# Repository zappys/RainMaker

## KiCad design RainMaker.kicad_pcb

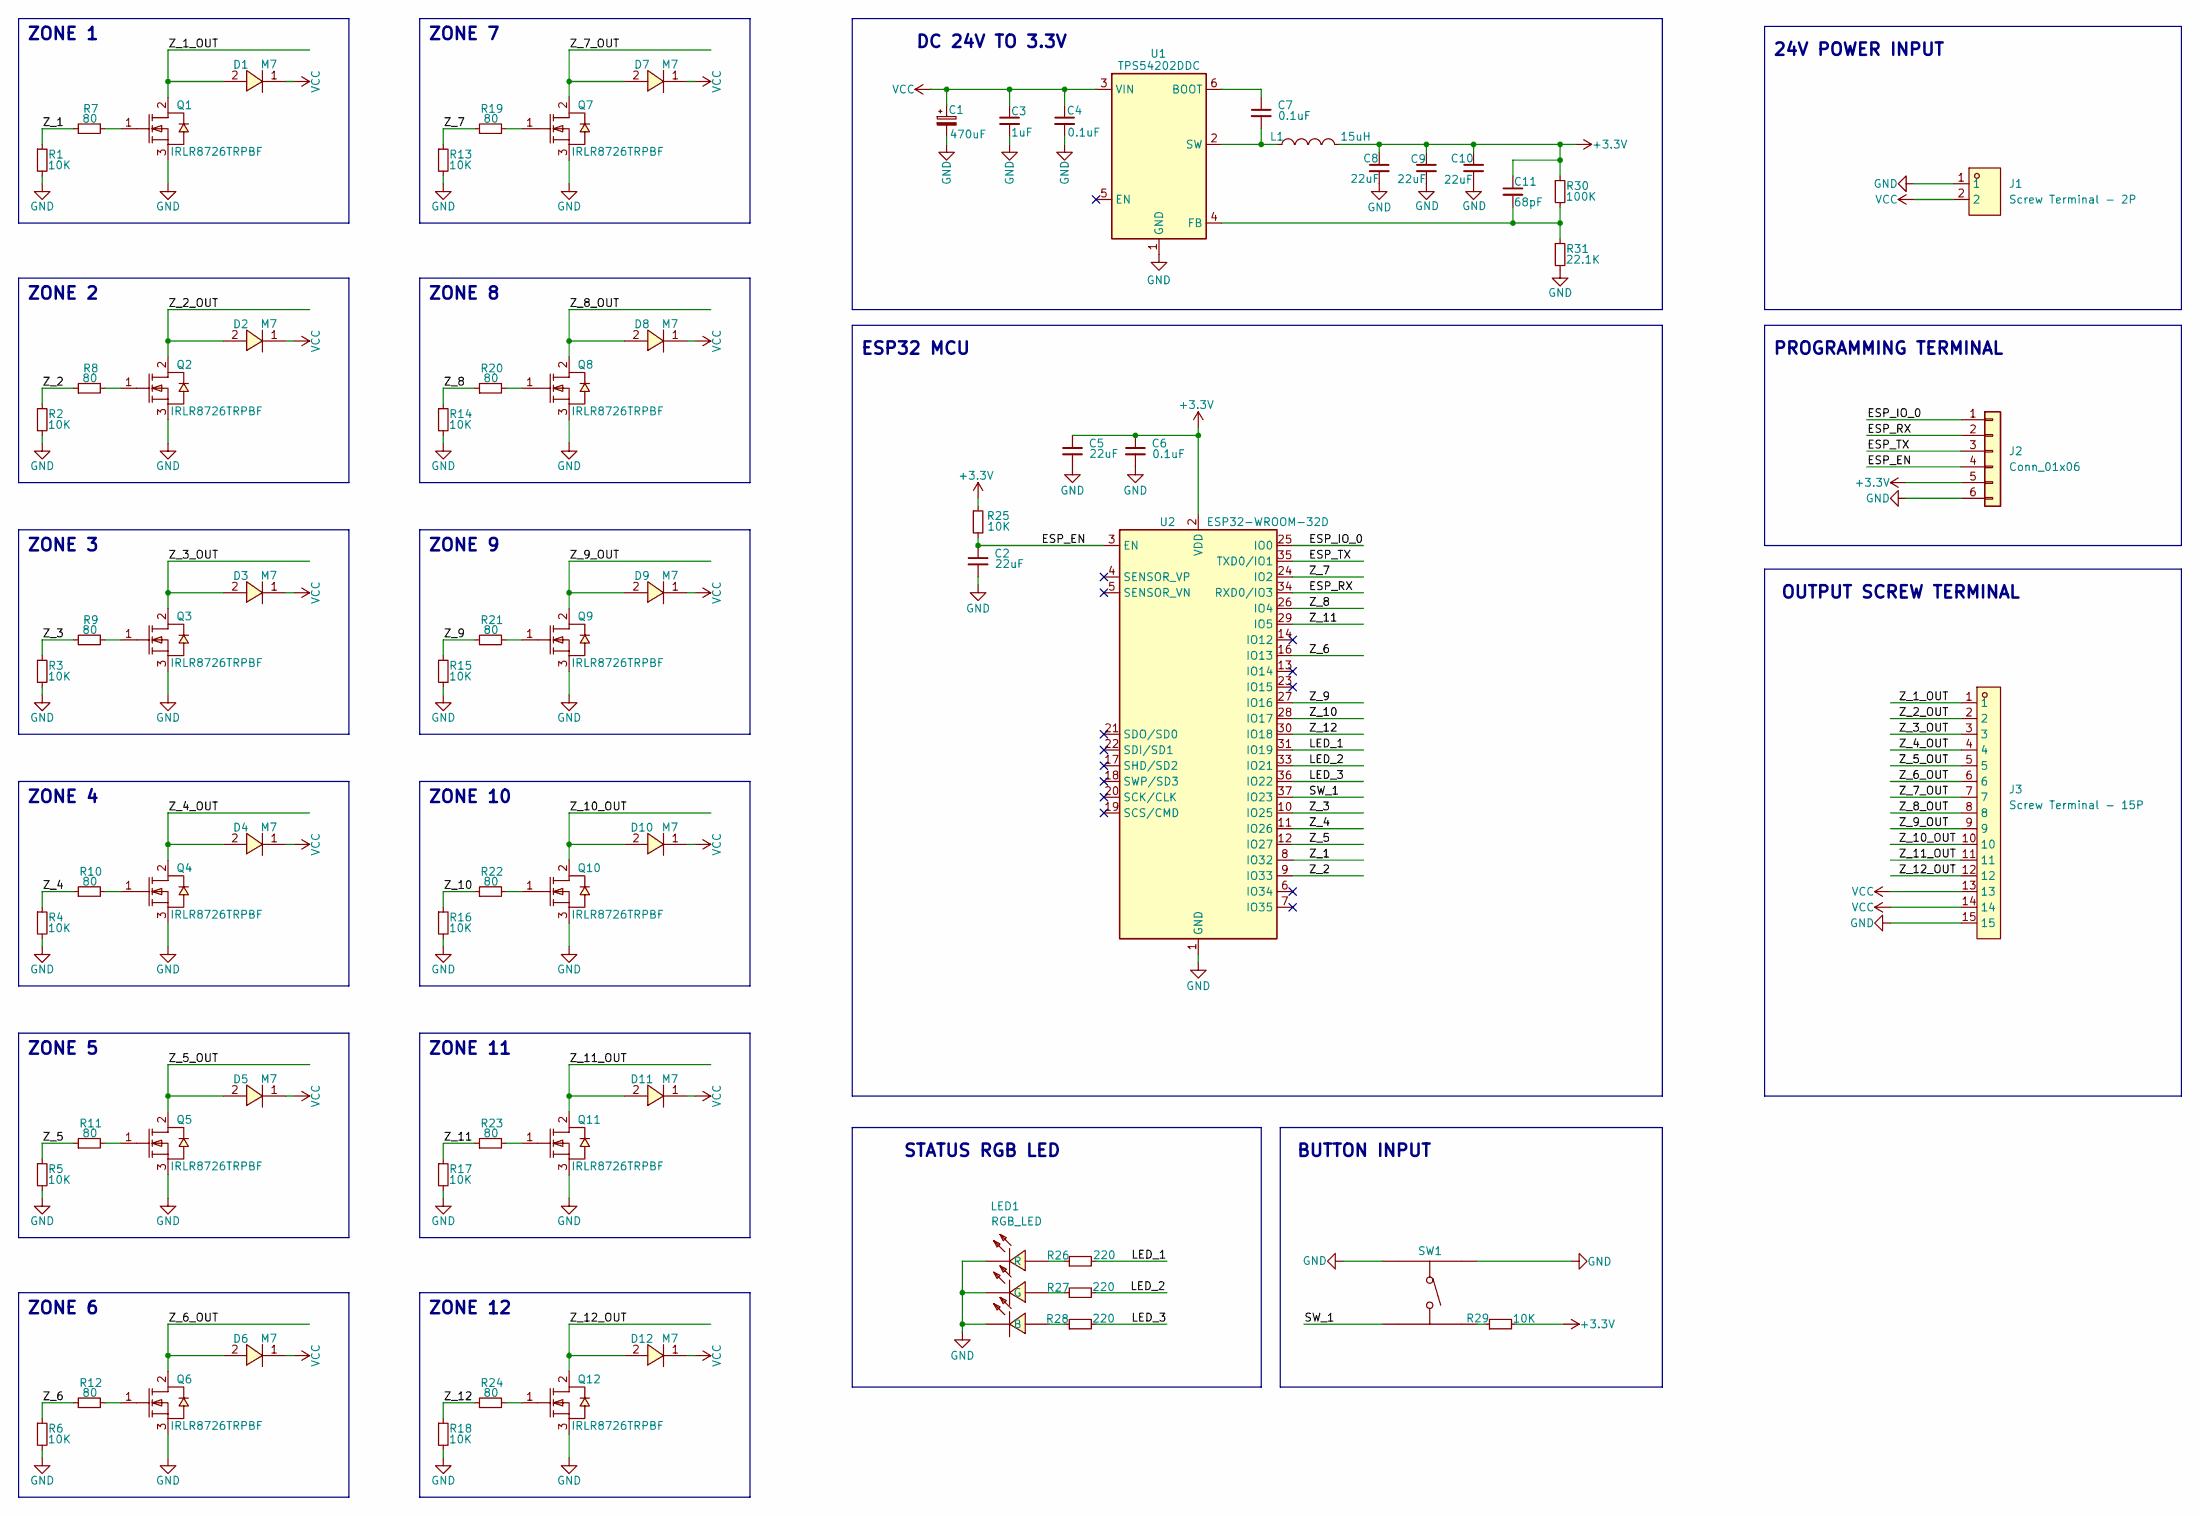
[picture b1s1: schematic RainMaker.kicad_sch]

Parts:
C1: 470uF; CP_Radial_D10.0mm_P5.00mm
C2, C5: 22uF; C_0805_2012Metric_Pad1.18x1.45mm_HandSolder
C3: 1uF; C_0805_2012Metric_Pad1.18x1.45mm_HandSolder
C4, C6, C7: 0.1uF; C_0805_2012Metric_Pad1.18x1.45mm_HandSolder
C8, C9, C10: 22uF; C_0805_2012Metric_Pad1.18x1.45mm_HandSolder; LCSC C45783
C11: 68pF; C_0805_2012Metric_Pad1.18x1.45mm_HandSolder
D1, D2, D3, D4, D5, D6, D7, D8, D9, D10, D11, D12: M7; SMA_L4.4-W2.6-LS5.0-RD; LCSC Part C426571
J1: Screw Terminal - 2P; CONN-TH_P5.08_KF128-5.08-2P; LCSC Part C474952
J2: Conn_01x06; PinHeader_1x06_P2.54mm_Vertical
J3: Screw Terminal - 15P; CONN-TH_15P-P5.00_DB128V; LCSC Part C424689
L1: 15uH; IND-SMD_L7.2-W6.6_GPSR07X0; LCSC Part C5189959
LED1: RGB_LED; LED-ARRAY-SMD_6P-L1.6-W1.6-TL; LCSC Part C131204
Q1, Q2, Q3, Q4, Q5, Q6, Q7, Q8, Q9, Q10, Q11, Q12: IRLR8726TRPBF; TO-252-2; LCSC Part C81137
R1, R2, R3, R4, R5, R6, R13, R14, R15, R16, R17, R18, R25, R29: 10K; R_0603_1608Metric
R7, R8, R9, R10, R11, R12, R19, R20, R21, R22, R23, R24: 80; R_0603_1608Metric
R26, R27, R28: 220; R_0603_1608Metric
R30: 100K; R_0603_1608Metric
R31: 22.1K; R_0603_1608Metric
SW1: UK-B0206-G5-250-JZ; KEY-SMD_4P-L4.5-W4.5-P3.00-LS7.5; LCSC Part C780491
U1: TPS54202DDC; SOT-23-6
U2: ESP32-WROOM-32D; ESP32-WROOM-32

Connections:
+3.3V: C5.1, C6.1, C8.1, C9.1, C10.1, C11.1, J2.5, L1.2, R25.1, R29.2, R30.1, U2.2 (VDD)
/ESP_EN: C2.1, J2.4, R25.2, U2.3 (EN)
/ESP_IO_0: J2.1, U2.25 (IO0)
/ESP_RX: J2.2, U2.34 (RXD0/IO3)
/ESP_TX: J2.3, U2.35 (TXD0/IO1)
/LED_1: R26.2, U2.31 (IO19)
/LED_2: R27.2, U2.33 (IO21)
/LED_3: R28.2, U2.36 (IO22)
/SW_1: SW1.3, U2.37 (IO23)
/Z_1: R1.1, R7.1, U2.8 (IO32)
/Z_1_OUT: D1.2, J3.1, Q1.2
/Z_2: R2.1, R8.1, U2.9 (IO33)
/Z_2_OUT: D2.2, J3.2, Q2.2
/Z_3: R3.1, R9.1, U2.10 (IO25)
/Z_3_OUT: D3.2, J3.3, Q3.2
/Z_4: R4.1, R10.1, U2.11 (IO26)
/Z_4_OUT: D4.2, J3.4, Q4.2
/Z_5: R5.1, R11.1, U2.12 (IO27)
/Z_5_OUT: D5.2, J3.5, Q5.2
/Z_6: R6.1, R12.1, U2.16 (IO13)
/Z_6_OUT: D6.2, J3.6, Q6.2
/Z_7: R13.1, R19.1, U2.24 (IO2)
/Z_7_OUT: D7.2, J3.7, Q7.2
/Z_8: R14.1, R20.1, U2.26 (IO4)
/Z_8_OUT: D8.2, J3.8, Q8.2
/Z_9: R15.1, R21.1, U2.27 (IO16)
/Z_9_OUT: D9.2, J3.9, Q9.2
/Z_10: R16.1, R22.1, U2.28 (IO17)
/Z_10_OUT: D10.2, J3.10, Q10.2
/Z_11: R17.1, R23.1, U2.29 (IO5)
/Z_11_OUT: D11.2, J3.11, Q11.2
/Z_12: R18.1, R24.1, U2.30 (IO18)
/Z_12_OUT: D12.2, J3.12, Q12.2
GND: C1.2, C2.2, C3.2, C4.2, C5.2, C6.2, C8.2, C9.2, C10.2, J1.1, J2.6, J3.15, LED1.1, LED1.2, LED1.3, Q1.3, Q2.3, Q3.3, Q4.3, Q5.3, Q6.3, Q7.3, Q8.3, Q9.3, Q10.3, Q11.3, Q12.3, R1.2, R2.2, R3.2, R4.2, R5.2, R6.2, R13.2, R14.2, R15.2, R16.2, R17.2, R18.2, R31.2, SW1.1, SW1.2, U1.1 (GND), U2.1 (GND), U2.15 (GND), U2.38 (GND), U2.39 (GND)
unnamed: LED1.6 (B), R28.1
unnamed: LED1.5 (G), R27.1
unnamed: LED1.4 (R), R26.1
unnamed: Q1.1, R7.2
unnamed: Q2.1, R8.2
unnamed: Q3.1, R9.2
unnamed: Q4.1, R10.2
unnamed: Q5.1, R11.2
unnamed: Q6.1, R12.2
unnamed: Q7.1, R19.2
unnamed: Q8.1, R20.2
unnamed: Q9.1, R21.2
unnamed: Q10.1, R22.2
unnamed: Q11.1, R23.2
unnamed: Q12.1, R24.2
unnamed: R29.1, SW1.4
unnamed: C7.1, U1.6 (BOOT)
unnamed: C11.2, R30.2, R31.1, U1.4 (FB)
unnamed: C7.2, L1.1, U1.2 (SW)
VCC: C1.1, C3.1, C4.1, D1.1, D2.1, D3.1, D4.1, D5.1, D6.1, D7.1, D8.1, D9.1, D10.1, D11.1, D12.1, J1.2, J3.13, J3.14, U1.3 (VIN)

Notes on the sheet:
ZONE 9
ZONE 3
ZONE 10
24V POWER INPUT
ZONE 7
ZONE 1
ZONE 4
ESP32 MCU
DC 24V TO 3.3V
STATUS RGB LED
ZONE 12
OUTPUT SCREW TERMINAL
ZONE 5
ZONE 6
ZONE 8
BUTTON INPUT
ZONE 11
ZONE 2
PROGRAMMING TERMINAL

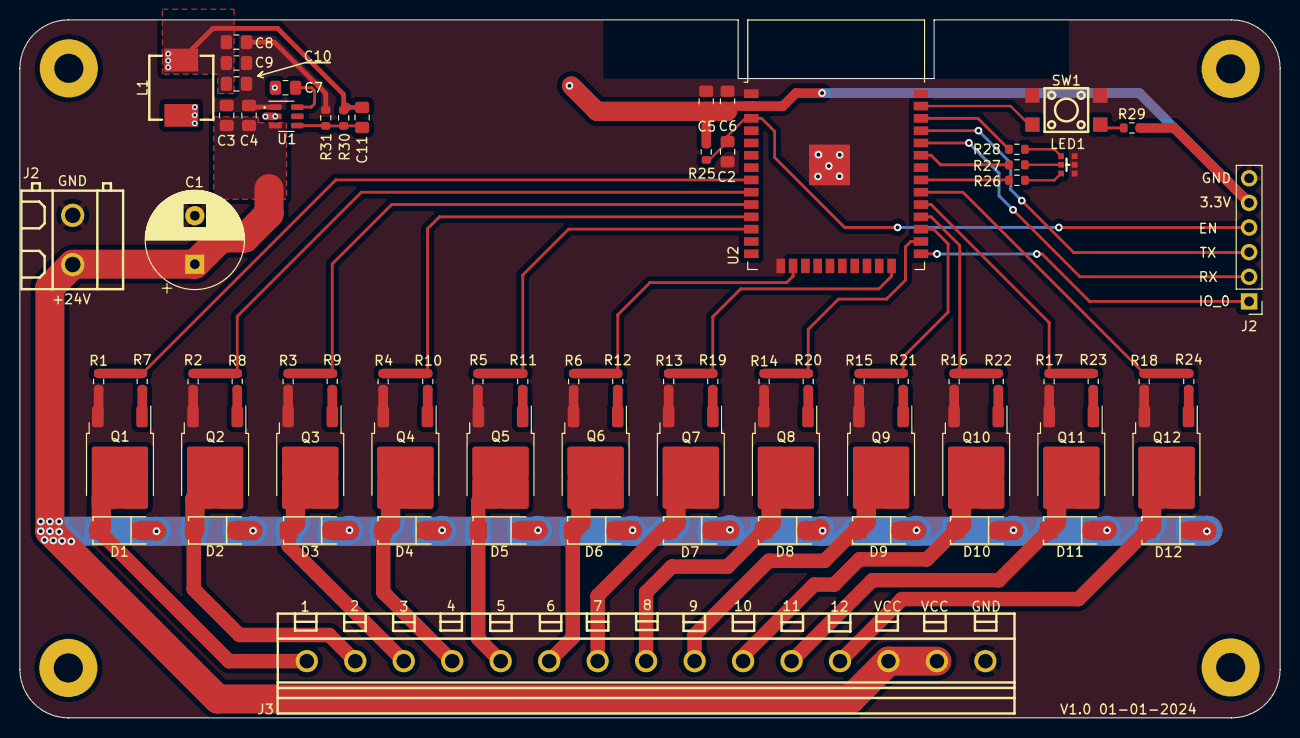
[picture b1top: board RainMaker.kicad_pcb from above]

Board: 2 copper layers, 130.0 x 72.0 mm, 74 parts (0 on the bottom side), 54 nets.

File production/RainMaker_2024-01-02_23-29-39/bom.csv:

Designator,Footprint,Quantity,Value,LCSC Part #
C1,CP_Radial_D10.0mm_P5.00mm,1,470uF,
"C10, C2, C5, C8, C9",0805,5,22uF,
C11,0805,1,68pF,
C3,0805,1,1uF,
"C4, C6, C7",0805,3,0.1uF,
"D1, D10, D11, D12, D2, D3, D4, D5, D6, D7, D8, D9",SMA_L4.4-W2.6-LS5.0-RD,12,M7,C426571
J1,CONN-TH_P5.08_KF128-5.08-2P,1,Screw Terminal - 2P,C474952
J2,PinHeader_1x06_P2.54mm_Vertical,1,Conn_01x06,
J3,CONN-TH_15P-P5.00_DB128V,1,Screw Terminal - 15P,C424689
L1,IND-SMD_L7.2-W6.6_GPSR07X0,1,15uH,C5189959
LED1,LED-ARRAY-SMD_6P-L1.6-W1.6-TL,1,RGB_LED,C131204
"Q1, Q10, Q11, Q12, Q2, Q3, Q4, Q5, Q6, Q7, Q8, Q9",TO-252-2,12,IRLR8726TRPBF,C81137
"R1, R13, R14, R15, R16, R17, R18, R2, R25, R29, R3, R4, R5, R6",0603,14,10K,
"R10, R11, R12, R19, R20, R21, R22, R23, R24, R7, R8, R9",0603,12,80,
"R26, R27, R28",0603,3,220,
R30,0603,1,100K,
R31,0603,1,22.1K,
SW1,KEY-SMD_4P-L4.5-W4.5-P3.00-LS7.5,1,UK-B0206-G5-250-JZ,C780491
U1,SOT-23-6,1,TPS54202DDC,
U2,ESP32-WROOM-32,1,ESP32-WROOM-32D,

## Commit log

2023-12-29 removed backups
2023-12-29 fix vcc
2023-12-29 fix unconnected
2023-12-31 fixes
2024-01-03 production files
